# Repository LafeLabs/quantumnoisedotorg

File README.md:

# [www.quantumnoise.org](https://www.quantumnoise.org)
# [github.com/lafelabs/quantumnoisedotorg/](https://github.com/lafelabs/quantumnoisedotorg/)

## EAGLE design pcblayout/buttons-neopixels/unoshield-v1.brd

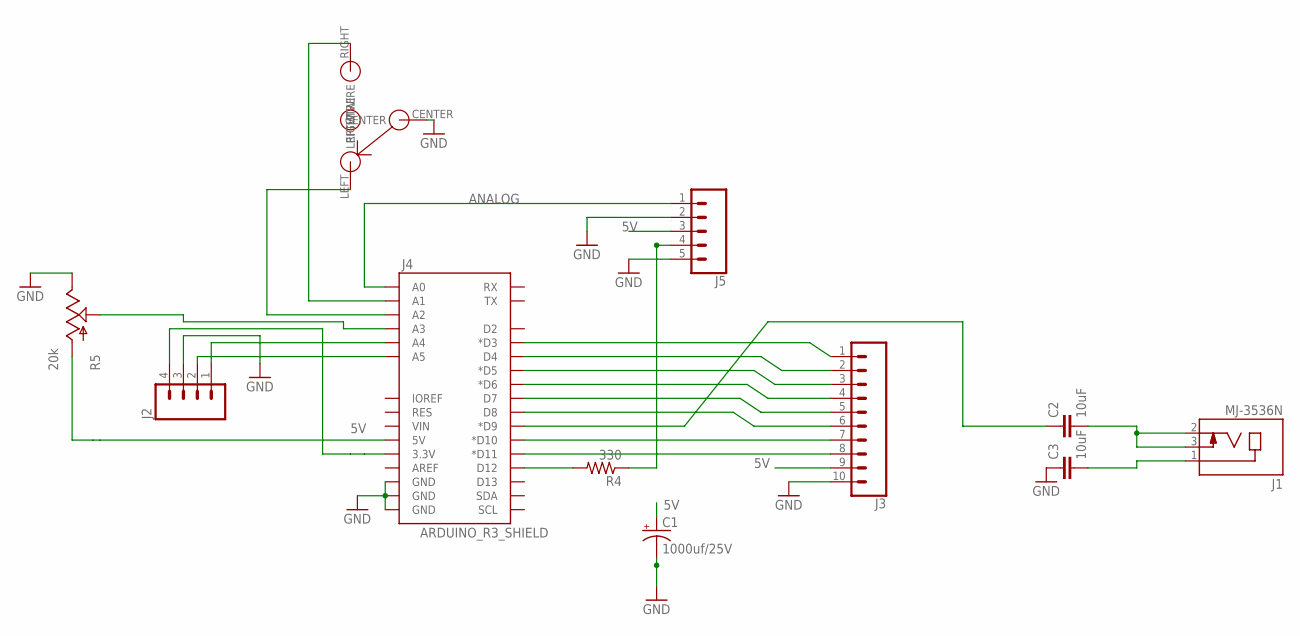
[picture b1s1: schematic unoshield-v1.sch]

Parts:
C1: 1000uf/25V; CPOL-RADIAL-1000UF-25V-KIT
C2, C3: 10uF; 0805
J1: MJ-3536N; CUI_MJ-3536N
J2: M04PTH; 1X04
J3: CONN_10"; 1X10
J4: ARDUINO_R3_SHIELD; UNO_R3_SHIELD
J5: CONN_05; 1X05
R4: 330; R0603
R5: 20k; ALPS_POT_KIT
SW3: ON-OFF-ON-360-1013-ND; 360-1013-ND

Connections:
5V: C1.+, J3.9, J4.5V, J5.3, R5.P$3 (A)
ANALOG: J4.A0, J5.1
BUTTON: J4.A1, SW3.RIGHT (RIGHTWIRE)
CL: J2.2, J4.A5
DA: J2.1, J4.A4
GND: C1.-, C3.1, J2.3, J3.10, J4.GND@0 (GND), J4.GND@1 (GND), J4.GND@2 (GND), J5.2, J5.5, R5.P$1 (E), SW3.CENTER
unnamed: J4.D12, R4.2
unnamed: J4.A3, R5.P$2 (S)
unnamed: J3.8, J4.D11 (*D11)
unnamed: J3.7, J4.D10 (*D10)
unnamed: J3.6, J4.D8
unnamed: J3.5, J4.D7
unnamed: J3.4, J4.D6 (*D6)
unnamed: J3.3, J4.D5 (*D5)
unnamed: J3.2, J4.D4
unnamed: J4.A2, SW3.LEFT (LEFTWIRE)
unnamed: J3.1, J4.D3 (*D3)
unnamed: C3.2, J1.1
unnamed: C2.2, J1.2, J1.3
unnamed: C2.1, J4.D9 (*D9)
unnamed: J5.4, R4.1
VCC: J2.4, J4.3.3V

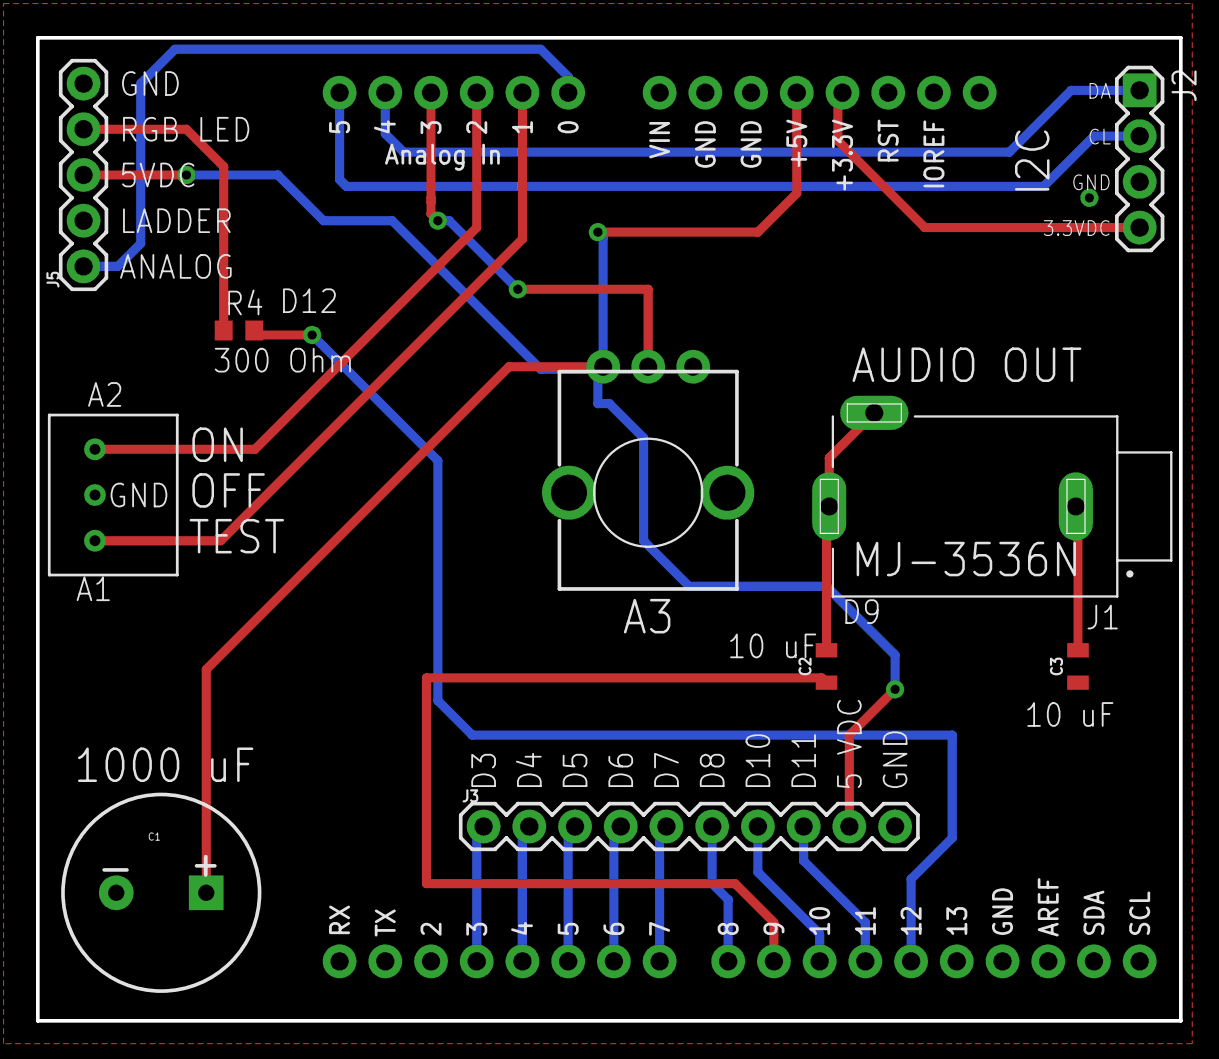
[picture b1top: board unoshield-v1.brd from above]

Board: 2 copper layers, 63.5 x 54.6 mm, 11 parts (0 on the bottom side), 22 nets.

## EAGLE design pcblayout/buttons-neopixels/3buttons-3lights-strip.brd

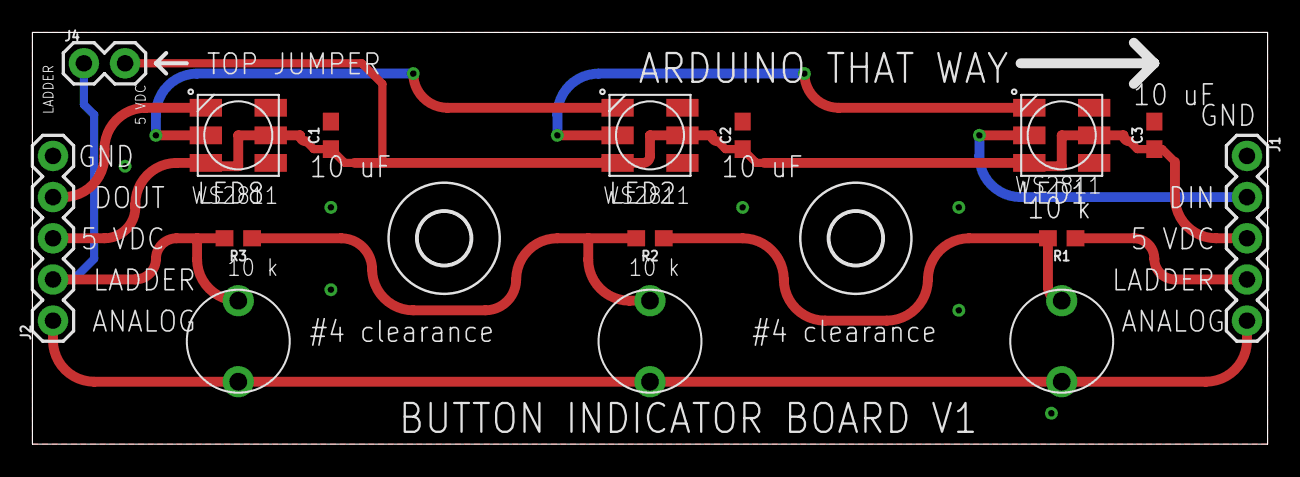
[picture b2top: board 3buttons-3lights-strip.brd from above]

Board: 2 copper layers, 76.2 x 25.4 mm, 17 parts (0 on the bottom side), 11 nets.

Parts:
C1, C2, C3: 10uF; 0603
H3, H4: MOUNT-HOLE3.2; 3,2
J1, J2: 1X05
J4: 1X02
LED1, LED2, LED8: WS28115050
R1, R2, R3: 10k; 0603
U$1, U$4, U$5: BUTTON

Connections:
+5V: C1.1, C2.1, C3.1, J1.3, J2.3, J4.2, LED1.LEDVDD, LED1.VDD, LED2.LEDVDD, LED2.VDD, LED8.LEDVDD, LED8.VDD
BUTTON: J1.5, J2.1, U$1.P$2, U$4.P$2, U$5.P$2
GND: C1.2, C2.2, C3.2, J1.1, J2.5, LED1.VSS, LED2.VSS, LED8.VSS
unnamed: LED1.DO, LED2.DI
unnamed: R1.2, R2.1, U$1.P$1
unnamed: R2.2, R3.1, U$4.P$1
unnamed: J2.2, J4.1, R3.2, U$5.P$1
unnamed: J1.4, R1.1
unnamed: LED2.DO, LED8.DI
unnamed: J1.2, LED1.DI
unnamed: J2.4, LED8.DO

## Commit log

2017-07-28 added a bare bones index.html
2017-07-28 added a menu
2017-07-30 writing the summary of what this project is all about(which is now on the web site)
2017-08-02 working on main site
2017-12-07 tons and tons of shit
2018-01-23 quantum noise dot org
2018-02-20 junction calculator with multiple equations in one
2018-03-08 like a million updates
2023-09-19 moved old version into old version folder
2023-09-19 update with live instance from raspberry pi
2023-09-20 working on the bill of materials for the output module at top of fridge
2023-09-21 added trash magic and figure
2023-09-21 replication of the global page
2023-09-21 really fleshing things out a lot more
2023-09-22 update the set from live
2023-09-23 adding more p5js applications which do useful things
2023-09-23 quantum scroll set work
2023-09-23 writing words
2023-09-24 graphs
2023-09-24 lots more figures
2023-09-24 Update home
2023-09-24 working on the filter
2023-09-24 filter section figure
2023-09-24 added more figures
2023-09-25 putting it all together, RC line filter almost there
2023-09-25 various parts for the packaging assembly
2023-09-25 various figures
2023-09-26 squares and replications and symbols
2023-09-27 the p5 set is insane. it's amazing.
2023-09-27 QNS spectra is a thing!
2023-09-27 box figures
2023-09-27 a bunch of the wrong scrolls got replicated, but maybe that's ok
2023-09-29 chaos
2023-09-29 Create tunnelprobe
2023-09-30 quantum trash? quantum trash
2023-10-01 replicating the geometron symbol set for the set of artifacts and documents
2023-10-01 added amp chain figure
2023-10-02 adding drawings
2023-10-02 changed name of a image file
2023-10-02 insertion loss of filter png added
2023-10-02 lots more layout files and also schematics
2023-10-03 moved writing around in main scroll
2023-10-03 scrolls work
2023-10-04 update dimensions in pcbdrawing.svg in trashmagic directory
2023-10-04 trash magic
2023-10-05 universal pcb layout in geometron now with correct spacing of pads
2023-10-05 adding of hand cut prototype pcb
2023-10-06 T.svg
2023-10-06 notpi.svg
2023-10-06 pcb layout, filters, figures
2023-10-07 slimezistor
2023-10-07 slimefilter!
2023-10-09 added links to smt components for filter and device capsule
2023-10-10 tilted washboard potential
2023-10-11 washboard work, failing to add runge kutta
2023-10-13 lots of things are happening all at once
2023-10-14 ramp2 is just about ready for re integration into the main document
2023-10-14 duplicating some figures, put the basic scroll into readme
2023-10-15 the book of noise!
2023-10-15 the book of noise
2023-10-15 it's all folded back into the main page now, which is the center of the QNS project
2023-10-16 SO MUCH CHAOS!!!! THIS IS CHAOS!
2023-10-16 more quantum madness
2023-10-17 blochchain
2023-10-17 Update blochchain
2023-10-17 bloch chain documentation, equations
2023-10-21 bloch chain 2d
2023-10-21 updating what now needs to go back and fix things
2023-10-21 JAWS
2023-10-22 self-replicating media!!! what?!?!
2023-10-22 ones and zeros of standard colors
2023-10-23 updates to bloch chain
2023-10-24 i hate computers and the industry which creates them as well as most people in that industry
2023-10-24 octal
2023-10-24 abjad gyrator 22
2023-10-24 Update sources
2023-10-24 adding more gyrators
2023-10-25 gyrator updates
2023-10-25 lots more gyrators
2023-10-27 bloch chain tarot
2023-10-27 merlock tarot
2023-10-28 MERLOCK tarot!
2023-10-28 we must create memes which dissolve the structures of power
2023-10-30 ammonia.html
2023-10-31 added maser like resonance to ammonia.html
2023-11-05 the BASS!!!! is added to analog DTMF generator
2023-12-03 rock n roll
2023-12-03 rock n roll!
2023-12-04 trash magic images
2023-12-09 added schematics
2023-12-09 noise modulator, jj. various things
2023-12-09 what happened here?
2023-12-10 tunneling animation
2023-12-16 tunneling animation updates
2023-12-19 graphene geometron symbols
2024-01-01 dial images

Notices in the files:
parts and their libraries:
microbuilder: This work is placed in the public domain, and may be freely used for commercial and non-commercial work with the following conditions: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
SparkFun-Resistors: Licensing: Creative Commons ShareAlike 4.0 International - https://creativecommons.org/licenses/by-sa/4.0
